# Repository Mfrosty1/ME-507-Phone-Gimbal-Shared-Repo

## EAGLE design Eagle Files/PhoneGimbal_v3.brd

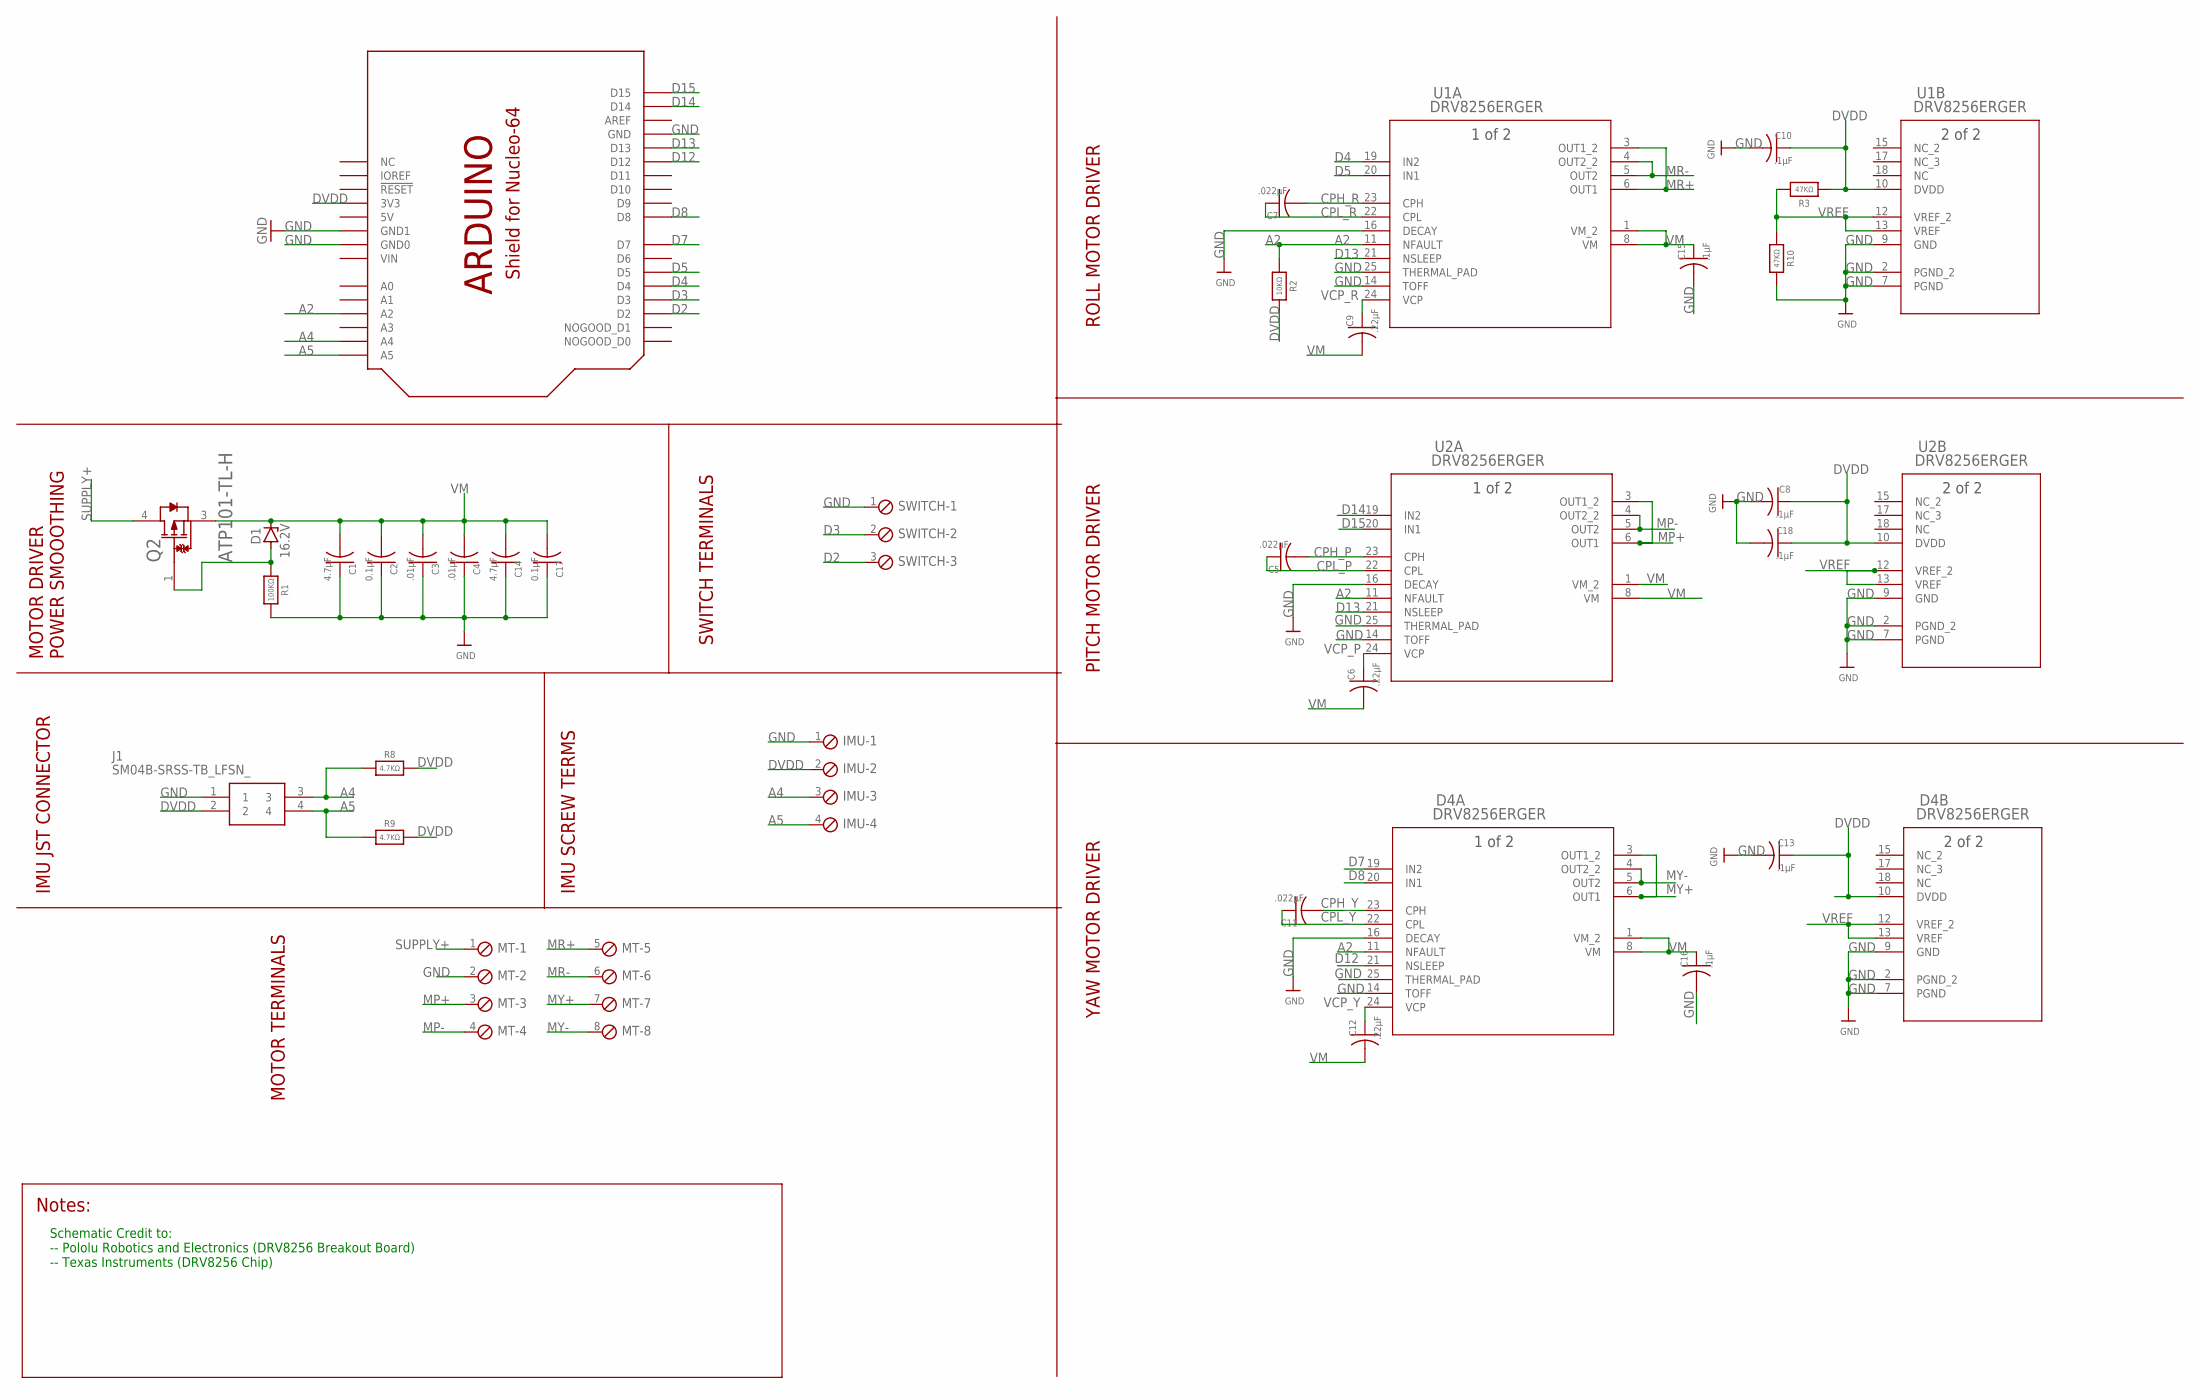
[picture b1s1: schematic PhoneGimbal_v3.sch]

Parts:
C1, C14: 4.7µF; C0805
C2, C17: 0.1µF; C0805
C3, C4: .01µF; C0805
C5, C7, C11: .022µF; C0805
C6, C9, C12: .22µF; C0805
C8, C10, C13, C15, C16, C18: .1µF; C0805
D1: 16.2V; DO34Z7
D4: DRV8256ERGER; VQFN_6PRGER_TEX
IMU: SCREWTERM_4P_254; 4POL254
J1: SM04B-SRSS-TB_LFSN_; SM04B-SRSS-TB(LFSN)
MT: SCREWTERM_8P_381; 8POL381
Q2: ON_SEMICONDUCTOR_ATP101-TL-HON_SEMICONDUCTOR_ATP1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; ON_SEMICONDUCTOR_ATP101-TL-H_0
R1: 100KΩ; _1206
R2: 10KΩ; _1206
R3, R10: 47KΩ; _1206
R8, R9: 4.7KΩ; _1206
SWITCH: SCREWTERM_3P_254; 3POL254
U1, U2: DRV8256ERGER; VQFN_6PRGER_TEX
U$1: SHIELD_FOR_NUCLE0_64_STANDARD; SHIELD_FOR_NUCLEO_64_STD

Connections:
5V: U$1.5V
A2: D4.11 (NFAULT), R2.1, U1.11 (NFAULT), U2.11 (NFAULT), U$1.A2
A4: IMU.3, J1.3, R8.1, U$1.A4
A5: IMU.4, J1.4, R9.1, U$1.A5
CPH_P: C5.2, U2.23 (CPH)
CPH_R: C7.2, U1.23 (CPH)
CPH_Y: C11.2, D4.23 (CPH)
CPL_P: C5.1, U2.22 (CPL)
CPL_R: C7.1, U1.22 (CPL)
CPL_Y: C11.1, D4.22 (CPL)
D2: SWITCH.3, U$1.D2
D3: SWITCH.2, U$1.D3
D4: U1.19 (IN2), U$1.D4
D5: U1.20 (IN1), U$1.D5
D7: D4.19 (IN2), U$1.D7
D8: D4.20 (IN1), U$1.D8
D12: D4.21 (NSLEEP), U$1.D12
D13: U1.21 (NSLEEP), U2.21 (NSLEEP), U$1.D13
D14: U2.19 (IN2), U$1.D14
D15: U2.20 (IN1), U$1.D15
DVDD: C8.1, C10.1, C13.1, C18.1, D4.10 (DVDD), IMU.2, J1.2, R2.2, R3.1, R8.2, R9.2, U1.10 (DVDD), U2.10 (DVDD), U$1.3V (3V3)
GND: C1.1, C2.1, C3.1, C4.1, C8.2, C10.2, C13.2, C14.1, C15.2, C16.2, C17.1, C18.2, D4.2 (PGND_2), D4.7 (PGND), D4.9 (GND), D4.14 (TOFF), D4.16 (DECAY), D4.25 (THERMAL_PAD), IMU.1, J1.1, MT.2, R1.2, R10.2, SWITCH.1, U1.2 (PGND_2), U1.7 (PGND), U1.9 (GND), U1.14 (TOFF), U1.16 (DECAY), U1.25 (THERMAL_PAD), U2.2 (PGND_2), U2.7 (PGND), U2.9 (GND), U2.14 (TOFF), U2.16 (DECAY), U2.25 (THERMAL_PAD), U$1.GND, U$1.GND1 (GND0), U$1.GND2 (GND1)
MP+: MT.3, U2.3 (OUT1_2), U2.6 (OUT1)
MP-: MT.4, U2.4 (OUT2_2), U2.5 (OUT2)
MR+: MT.5, U1.3 (OUT1_2), U1.6 (OUT1)
MR-: MT.6, U1.4 (OUT2_2), U1.5 (OUT2)
MY+: D4.3 (OUT1_2), D4.6 (OUT1), MT.7
MY-: D4.4 (OUT2_2), D4.5 (OUT2), MT.8
unnamed: D1.A, Q2.1 (G), R1.1
SUPPLY+: MT.1, Q2.4 (D)
VCP_P: C6.1, U2.24 (VCP)
VCP_R: C9.1, U1.24 (VCP)
VCP_Y: C12.1, D4.24 (VCP)
VIN: U$1.VIN
VM: C1.2, C2.2, C3.2, C4.2, C6.2, C9.2, C12.2, C14.2, C15.1, C16.1, C17.2, D1.C, D4.1 (VM_2), D4.8 (VM), Q2.3 (S), U1.1 (VM_2), U1.8 (VM), U2.1 (VM_2), U2.8 (VM)
VREF: D4.12 (VREF_2), D4.13 (VREF), R3.2, R10.1, U1.12 (VREF_2), U1.13 (VREF), U2.12 (VREF_2), U2.13 (VREF)

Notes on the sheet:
ROLL MOTOR DRIVER
PITCH MOTOR DRIVER
YAW MOTOR DRIVER
MOTOR DRIVER POWER SMOOOTHING
IMU JST CONNECTOR
MOTOR TERMINALS
SWITCH TERMINALS
IMU SCREW TERMS
Schematic Credit to: -- Pololu Robotics and Electronics (DRV8256 Breakout Board) -- Texas Instruments (DRV8256 Chip)

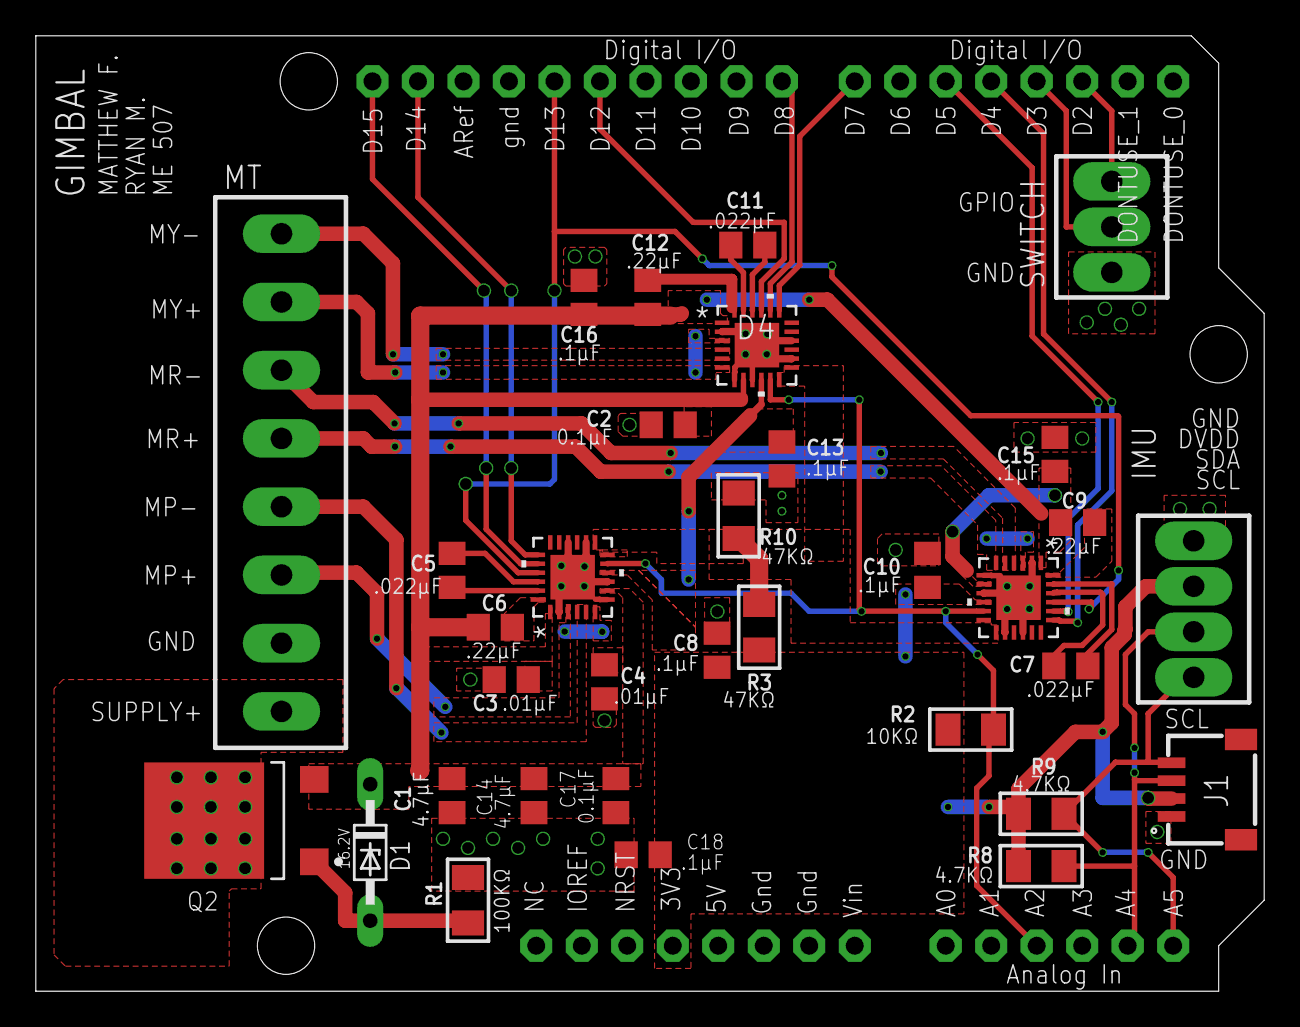
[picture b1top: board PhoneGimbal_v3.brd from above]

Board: 2 copper layers, 68.6 x 53.3 mm, 34 parts (0 on the bottom side), 34 nets.

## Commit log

2021-10-28 init commit
2021-10-28 testing a change to commit and push
2021-10-28 adding ICM20948 files
2021-10-29 Got the I2C working with pins A4 and A5
2021-10-31 adding motor driver test
2021-10-31 changed name of main for IMU test
2021-10-31 adding new motor driver files
2021-10-31 driver
2021-11-01 ryan trying a commit
2021-11-01 ryan attempting to commit
2021-11-01 attempt 3
2021-11-01 added my stuff from yesterday in a new file
2021-11-01 before 11/1
2021-11-01 changed file names
2021-11-01 just did this
2021-11-01 small changes
2021-11-01 pre-office hours
2021-11-01 test code
2021-11-01 slight changes to main
2021-11-02 Got motor running with only hardware. Editing code to get it with software
2021-11-02 starting to try and get motor to spin after successful hardware test.
2021-11-02 Got a motor to spin!
2021-11-04 Got motors to spin with the class!
2021-11-04 Little touch ups
2021-11-06 added methods to .h file
2021-11-06 Added PID.h and PID.cpp, initial controller class files
2021-11-06 Got IMU task set up to interact with class. Think I got shares to work.
2021-11-09 Set up part of motor task
2021-11-10 update, moveMotor written
2021-11-10 added a task for PID controller, and added a method to PID class for user inputs
2021-11-10 documentation
2021-11-10 modified DRV8256.h to fix an error
2021-11-10 continued working on classes
2021-11-10 controller updates
2021-11-10 about to do first test
2021-11-10 commented out serial stuff in controller
2021-11-10 initial controller inputs added
2021-11-10 PID updates
2021-11-10 changed printing method for PID task
2021-11-10 modification to print statemetns
2021-11-10 minor changes
2021-11-10 pid.cpp changes
2021-11-10 pid debugging
2021-11-10 debugging
2021-11-10 before class, teting stil giving nan
2021-11-10 trying to debug nan still
2021-11-10 MORE DEBUGGING
2021-11-10 debug
2021-11-10 atan2 debug
2021-11-10 quaternions debug
2021-11-10 testing still not working from gimbal lock
2021-11-11 Put code to prevent nan going to controller. IMU seems to be freaking out less
2021-11-12 Testing with actual motor started.
2021-11-12 fixed roll/yaw angle mixup. Next should try making the tasks faster to avoid buzzing sound.
2021-11-13 testing with external motor to get directions figured out. Can't go past like 10-15 degrees in roll negative direction without the motor either starting to beep or stay at a constant value.
2021-11-15 still having the issue. Seems to be when current is flipping
2021-11-17 Thought we got it working. Seems to be with IMU and maybe the quaternion output
2021-11-18 Still not working. Have tried a new board (no luck) and endTransmission(false) with no luck
2021-11-18 Got the BNO to work!
2021-11-18 IMU working with motor tasks
2021-11-22 Got directions correct for motors and angles with BNO
2021-11-22 Started with custom PCB and got pitch/yaw to work (hopefully) at the same time.
2021-11-23 Cleaned up code, all three seem to be functioning but tuning has not begun yet
2021-11-27 Tuned each of the three axes
2021-11-27 added yaw into the mix for all three to be going at the same time.
2021-11-28 tuning continued. Fixed yaw offset issue
2021-11-28 removed comments/old code
2021-11-29 roll seems to be working better with an offset of 20
2021-11-29 roll doing well, pitch needs some more work
2021-11-30 pitch working better to disturbances. vTaskDelays reduced
2021-12-01 added docs/
2021-12-01 trying doxygen
2021-12-01 testing
2021-12-01 attempt at adding logo
2021-12-01 logo attempt 2
2021-12-01 attempt 4
2021-12-01 changing doxygen portfolio name
2021-12-01 changing name
2021-12-01 adsf
2021-12-01 output text direction =
2021-12-01 OUTPUT_TEXT_DIRECTION = None
2021-12-01 documented a few more variables
2021-12-01 Fixed doxygen stuff and got data printing
2021-12-01 deleted old files (ICM stuff) and documented after turning on RECURSIVE
2021-12-01 testing completed
2021-12-02 Doxygen done?
2021-12-02 doxygen pushed
2021-12-02 ryan's doxyfile
2021-12-02 ryan doxyfile
2021-12-02 testing with ryan's Doxyfile
2021-12-02 test 2
2021-12-02 test 3
2021-12-02 test 4
2021-12-02 test 5
2021-12-02 removed matthew's doxygen stuff
2021-12-02 test 7
2021-12-02 TEST 8
2021-12-02 test 9
2021-12-02 adding new lgo
2021-12-02 test 10
2021-12-03 addign eagle files

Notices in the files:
parts and their libraries:
microbuilder: This work is placed in the public domain, and may be freely used for commercial and non-commercial work with the following conditions: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
COPYRIGHT: Copyright (C) 2018 Accelerated Designs. All rights reserved
